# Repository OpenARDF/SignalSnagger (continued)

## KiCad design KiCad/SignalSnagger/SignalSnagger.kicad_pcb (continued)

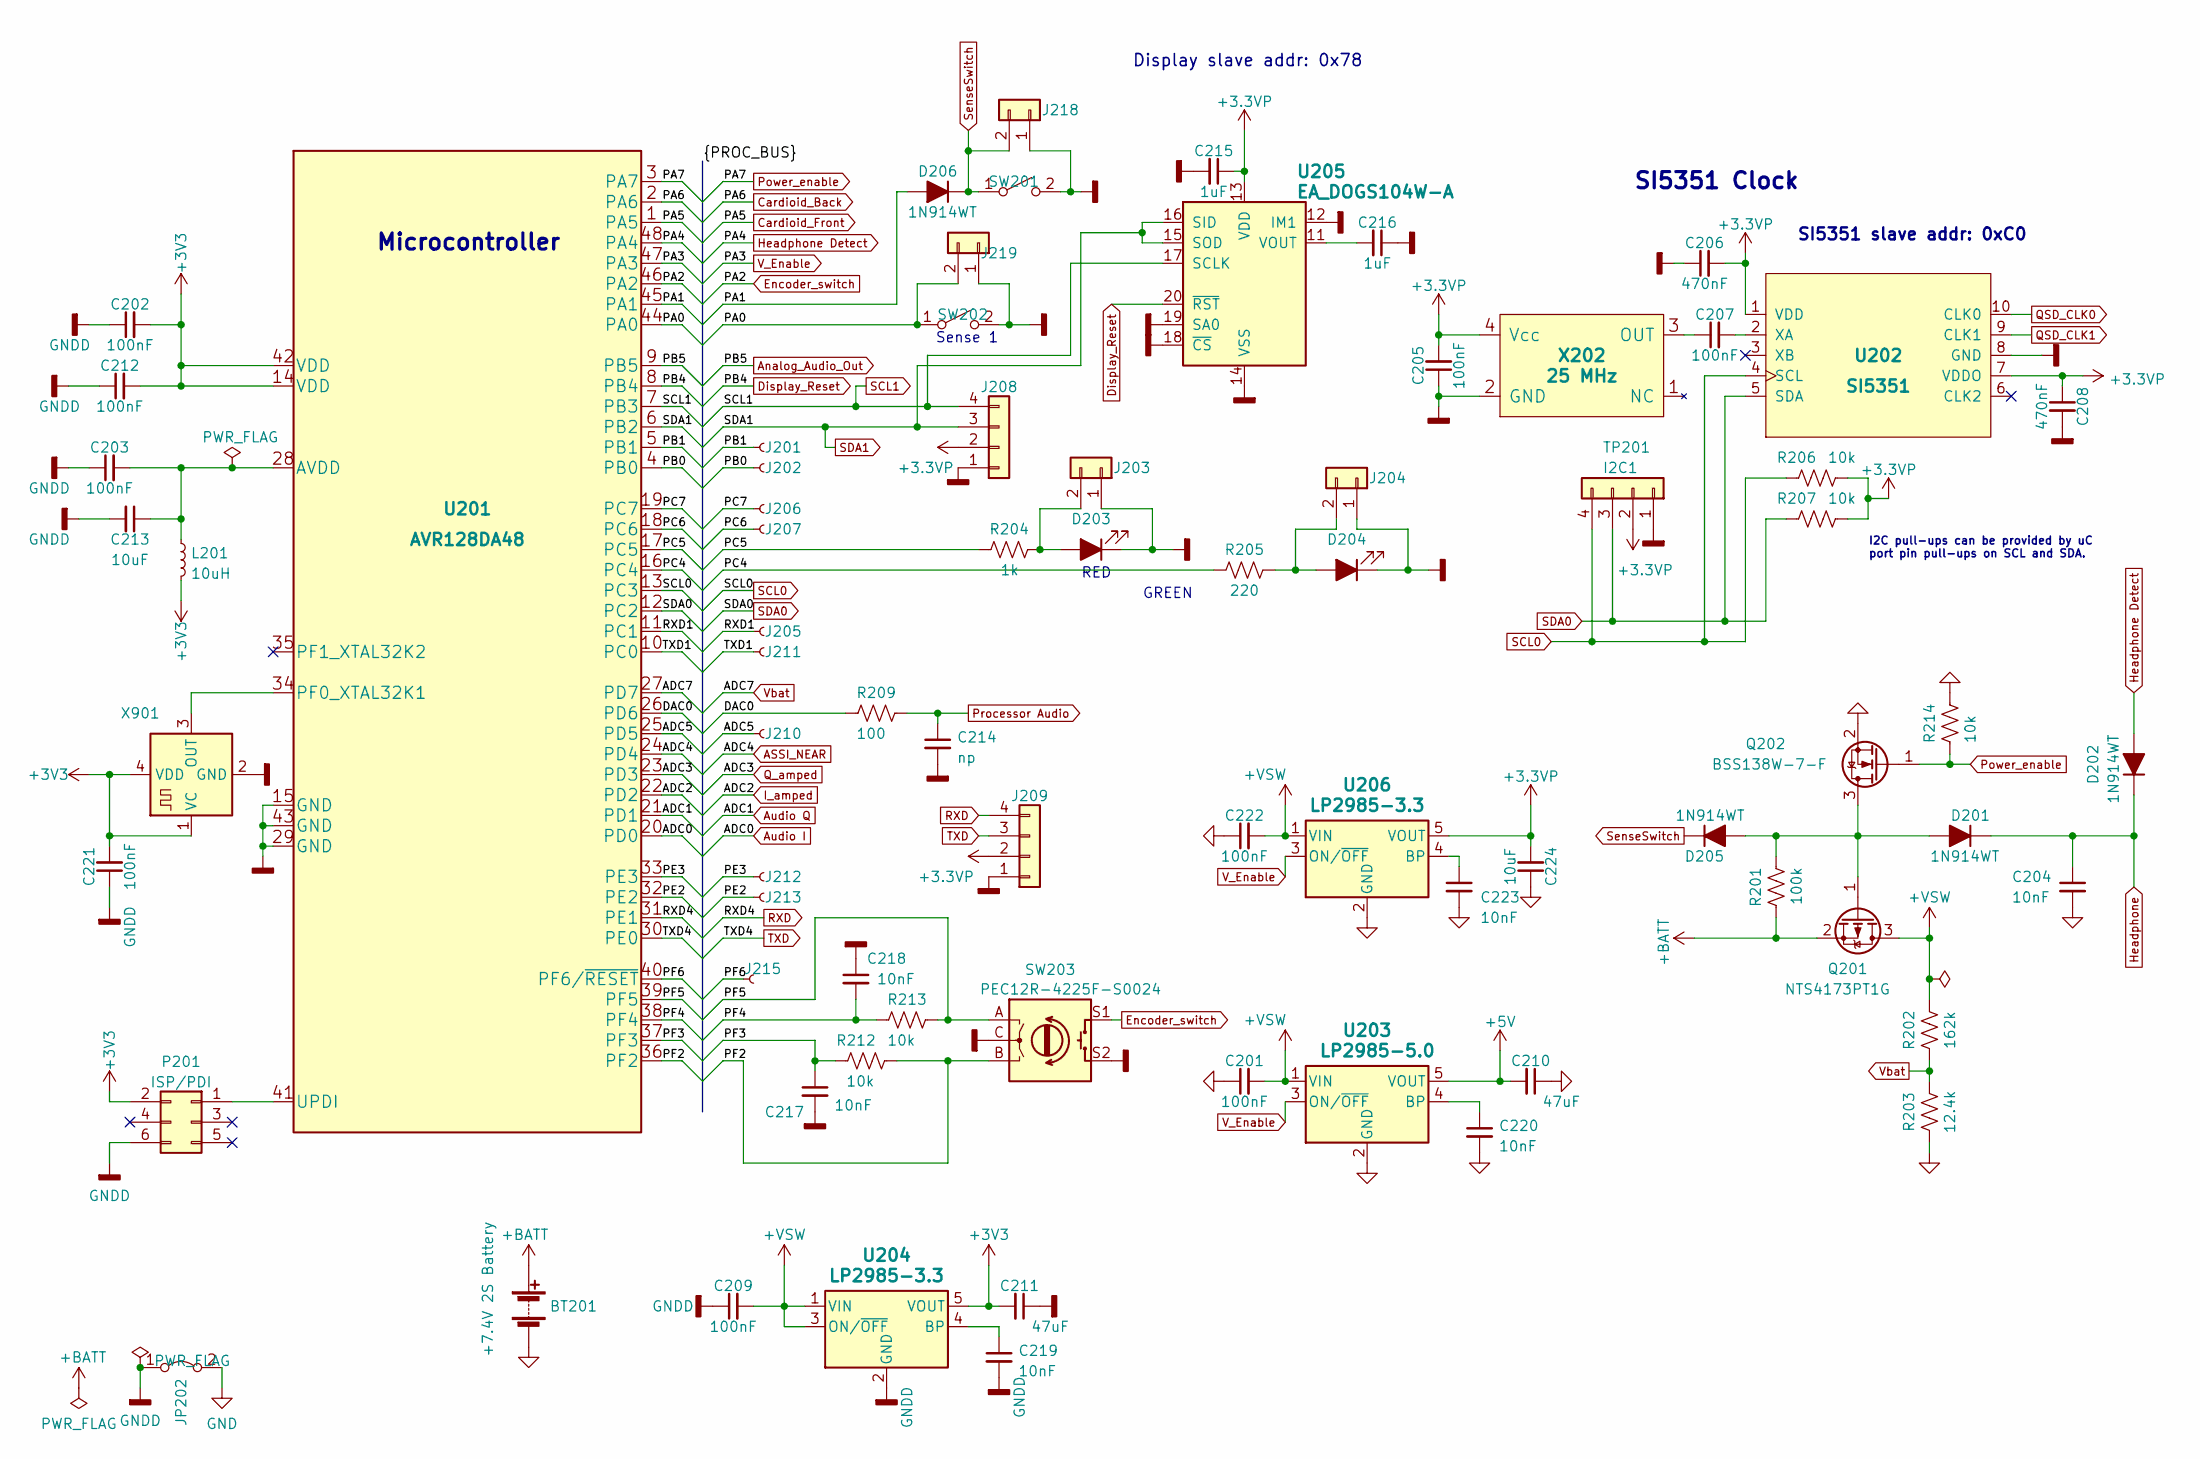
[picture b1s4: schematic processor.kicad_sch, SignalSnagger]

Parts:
BT201: +7.4V 2S Battery; SolderWire-1sqmm_1x02_P7.8mm_D1.4mm_OD3.9mm_Relief; Digi-Key Part No. NP
C201, C202, C203, C205, C207, C209, C212, C221, C222: 100nF; C_0603_1608Metric; Manufacturer PN CL10B104KA8NNNC; Digi-Key Part No. 1276-1006-1-ND
C204, C217, C218, C219, C220, C223: 10nF; C_0603_1608Metric; Manufacturer PN GRM1885C1H103JA01D; Digi-Key Part No. 490-9666-1-ND
C206, C208: 470nF; C_0603_1608Metric; Manufacturer PN CL10B474KA8VPJC; Digi-Key Part No. 1276-CL10B474KA8VPJCCT-ND
C210, C211: 47uF; C_1210_3225Metric; Manufacturer PN CL32A476KOJNNNE; Digi-Key Part No. 1276-3376-1-ND
C213, C224: 10uF; C_0603_1608Metric; Manufacturer PN GRM188C81C106MA73D; Digi-Key Part No. 490-7198-1-ND
C214: np; C_0603_1608Metric; Manufacturer PN C0603X103J4HACAUTO; Digi-Key Part No. 399-C0603X103J4HACAUTOCT-ND
C215, C216: 1uF; C_0603_1608Metric; Manufacturer PN CC0603KRX5R8BB105; Digi-Key Part No. 311-1445-1-ND
D201, D202, D205, D206: 1N914WT; D_SOD-523; Manufacturer PN 1N4148WT-7; Digi-Key Part No. 1N4148WTDICT-ND
D203: Red LED; LED_0805_2012Metric; Manufacturer PN LTST-C170KRKT; Digi-Key Part No. 160-1415-1-ND
D204: Green LED; LED_0805_2012Metric; Manufacturer PN LTST-C170KGKT; Digi-Key Part No. 160-1414-1-ND
J201, J202, J205, J206, J207, J210, J211, J212, J213, J215: Conn_01x01_Female; Dummy_Empty
J203, J204, J218, J219: Conn_01x02; PinSocket_1x02_P1.27mm_Vertical; Digi-Key Part No. N/P
J208, J209: Conn_01x04; PinHeader_1x04_P1.27mm_Vertical
JP202: Jumper_2_Bridged; Jumper_THT-1x02_Bridged_Circular; Digi-Key Part No. N/P
L201: 10uH; L_0603_1608Metric; Manufacturer PN LBMF1608T100K; Digi-Key Part No. 587-1714-1-ND
P201: ISP/PDI; PinHeader_2x03_P2.54mm_Vertical_SMD; Manufacturer PN M20-8760442; Digi-Key Part No. M20-8760442-ND
Q201: NTS4173PT1G; SOT-323_SC-70; Manufacturer PN NTS4173PT1G; Digi-Key Part No. NTS4173PT1GOSCT-ND
Q202: BSS138W-7-F; SOT-323_SC-70; Manufacturer PN BSS138W-7-F; Digi-Key Part No. BSS138W-FDICT-ND
R201: 100k; R_0603_1608Metric; Manufacturer PN RC0603FR-07100KL; Digi-Key Part No. 311-100KHRCT-ND
R202: 162k; R_0603_1608Metric; Manufacturer PN RC0603FR-07162KL; Digi-Key Part No. 311-162KHRCT-ND
R203: 12.4k; R_0603_1608Metric; Manufacturer PN RC0603FR-0712K4L; Digi-Key Part No. 311-12.4KHRCT-ND
R204: 1k; R_0603_1608Metric; Manufacturer PN RC0603FR-071KL; Digi-Key Part No. 311-1.00KHRCT-ND
R205: 220; R_0603_1608Metric; Manufacturer PN RC0603FR-07220RL; Digi-Key Part No. 311-220HRCT-ND
R206, R207, R212, R213, R214: 10k; R_0603_1608Metric; Manufacturer PN RC0603FR-0710KL; Digi-Key Part No. 311-10.0KHRCT-ND
R209: 100; R_0603_1608Metric; Manufacturer PN RC0603FR-07100RL; Digi-Key Part No. 311-100HRCT-ND
SW201, SW202: SW_SPST; SW_SPST_TL1014BF160QG; Manufacturer PN TL1014BF160QG; Digi-Key Part No. EG5042CT-ND
SW203: PEC12R-4225F-S0024; RotaryEncoder_Bourns_PEC12R-Switch_Vertical_CircularMountin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; Manufacturer PN PEC12R-4225F-S0024; Digi-Key Part No. PEC12R-4225F-S0024-ND
TP201: I2C1; PinSocket_1x04_P1.27mm_Vertical; Digi-Key Part No. N/P
U201: AVR128DA48; TQFP-48_7x7mm_P0.5mm; Manufacturer PN AVR128DA48T-E/PT; Digi-Key Part No. 150-AVR128DA48T-E/PTCT-ND
U202: SI5351; MSOP-10_3x3mm_P0.5mm; Manufacturer PN SI5351A-B-GT; Digi-Key Part No. 336-2399-5-ND
U203: LP2985-5.0; SOT-23-5; Manufacturer PN LP2985-50DBVR; Digi-Key Part No. 296-20717-1-ND
U204, U206: LP2985-3.3; SOT-23-5; Manufacturer PN LP2985-33DBVR; Digi-Key Part No. 296-18476-1-ND
U205: EA_DOGS104W-A; EA_DOGS104X-A; Manufacturer PN EA DOGS104W-A; Digi-Key Part No. 1481-1233-ND
X202: 25 MHz; Crystal_SMD_TXETCLSANF-4Pin; Manufacturer PN TXETCLSANF-25.000000; Digi-Key Part No. 1664-1273-1-ND
X901: ECS-327TXO-30-TR; Oscillator_SMD_ECS_327TXO; Manufacturer PN ECS-327TXO-30-TR; Digi-Key Part No. 50-ECS-327TXO-30-CT-ND

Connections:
+3.3VP: C205.2, C206.2, C208.1, C215.1, C224.2, J208.2, J209.2, R206.1, R207.1, TP201.2, U202.1 (VDD), U202.7 (VDDO), U205.13 (VDD), U206.5 (VOUT), X202.4 (Vcc)
+3V3: C202.2, C211.2, C212.2, C221.2, L201.2, P201.2, U201.14 (VDD), U201.42 (VDD), U204.5 (VOUT), X901.1 (VC), X901.4 (VDD)
+5V: C210.2, U203.5 (VOUT); also elsewhere on the board
+BATT: BT201.2 (+), Q201.2 (S), R201.1
+VSW: C201.2, C209.2, C222.2, Q201.3 (D), R202.2, U203.1 (VIN), U204.1 (VIN), U204.3 (ON/~OFF), U206.1 (VIN); also elsewhere on the board
/Processor/ADC5: J210.1, U201.25 (PD5)
/Processor/DAC0: R209.1, U201.26 (PD6)
/Processor/PA0: J219.2, SW202.1 (A), U201.44 (PA0)
/Processor/PA1: D206.2 (A), U201.45 (PA1)
/Processor/PB0: J202.1, U201.4 (PB0)
/Processor/PB1: J201.1, U201.5 (PB1)
/Processor/PC4: R205.1, U201.16 (PC4)
/Processor/PC5: R204.1, U201.17 (PC5)
/Processor/PC6: J207.1, U201.18 (PC6)
/Processor/PC7: J206.1, U201.19 (PC7)
/Processor/PE2: J213.1, U201.32 (PE2)
/Processor/PE3: J212.1, U201.33 (PE3)
/Processor/PF2: R212.1, SW203.B, U201.36 (PF2)
/Processor/PF3: C217.1, R212.2, U201.37 (PF3)
/Processor/PF4: C218.2, R213.2, U201.38 (PF4)
/Processor/PF5: R213.1, SW203.A, U201.39 (PF5)
/Processor/PF6: J215.1, U201.40 (PF6/~RESET)
/Processor/RXD1: J205.1, U201.11 (PC1)
/Processor/TXD1: J211.1, U201.10 (PC0)
ASSI_NEAR: U201.24 (PD4); also elsewhere on the board
Analog_Audio_Out: U201.9 (PB5); also elsewhere on the board
Audio I: U201.20 (PD0); also elsewhere on the board
Audio Q: U201.21 (PD1); also elsewhere on the board
Cardioid_Back: U201.2 (PA6); also elsewhere on the board
Cardioid_Front: U201.1 (PA5); also elsewhere on the board
Display_Reset: U201.8 (PB4), U205.20 (~RST)
Encoder_switch: SW203.S1, U201.46 (PA2)
GND: BT201.1 (-), C201.1, C204.2, C210.1, C220.2, C222.1, C223.2, C224.1, JP202.2 (B), Q202.2 (S), R203.1, R214.1, U203.2 (GND), U206.2 (GND); also elsewhere on the board
GNDD: C202.1, C203.1, C205.1, C206.1, C208.2, C209.1, C211.1, C212.1, C213.2, C214.2, C215.2, C216.1, C217.2, C218.1, C219.2, C221.1, D203.1 (K), D204.1 (K), J203.1, J204.1, J208.1, J209.1, J218.1, J219.1, JP202.1 (A), P201.6, SW201.2 (B), SW202.2 (B), SW203.C, SW203.S2, TP201.1, U201.15 (GND), U201.29 (GND), U201.43 (GND), U202.8 (GND), U204.2 (GND), U205.12 (IM1), U205.14 (VSS), U205.18 (~CS), U205.19 (SA0), X202.2 (GND), X901.2 (GND)
Headphone: C204.1, D201.1 (K), D202.1 (K); also elsewhere on the board
Headphone Detect: D202.2 (A), U201.48 (PA4)
I_amped: U201.22 (PD2); also elsewhere on the board
unnamed: D201.2 (A), D205.2 (A), Q201.1 (G), Q202.3 (D), R201.2
unnamed: D203.2 (A), J203.2, R204.2
unnamed: D204.2 (A), J204.2, R205.2
unnamed: P201.1, U201.41 (UPDI)
unnamed: C203.2, C213.1, L201.1, U201.28 (AVDD)
unnamed: U201.34 (PF0_XTAL32K1), X901.3 (OUT)
unnamed: C207.2, U202.2 (XA)
unnamed: C220.1, U203.4 (BP)
unnamed: C219.1, U204.4 (BP)
unnamed: C216.2, U205.11 (VOUT)
unnamed: C223.1, U206.4 (BP)
unnamed: C207.1, X202.3 (OUT)
Power_enable: Q202.1 (G), R214.2, U201.3 (PA7)
Processor Audio: C214.1, R209.2; also elsewhere on the board
QSD_CLK0: U202.10 (CLK0); also elsewhere on the board
QSD_CLK1: U202.9 (CLK1); also elsewhere on the board
Q_amped: U201.23 (PD3); also elsewhere on the board
RXD: J209.4, U201.31 (PE1)
SCL0: R206.2, TP201.4, U201.13 (PC3), U202.4 (SCL); also elsewhere on the board
SCL1: J208.4, U201.7 (PB3), U205.17 (SCLK); also elsewhere on the board
SDA0: R207.2, TP201.3, U201.12 (PC2), U202.5 (SDA); also elsewhere on the board
SDA1: J208.3, U201.6 (PB2), U205.15 (SOD), U205.16 (SID); also elsewhere on the board
SenseSwitch: D205.1 (K), D206.1 (K), J218.2, SW201.1 (A)
TXD: J209.3, U201.30 (PE0)
V_Enable: U201.47 (PA3), U203.3 (ON/~OFF), U206.3 (ON/~OFF)
Vbat: R202.1, R203.2, U201.27 (PD7)

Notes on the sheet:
I2C pull-ups can be provided by uC port pin pull-ups on SCL and SDA.
GREEN
Display slave addr: 0x78
Sense 1
RED
SI5351 slave addr: 0xC0
Microcontroller
SI5351 Clock

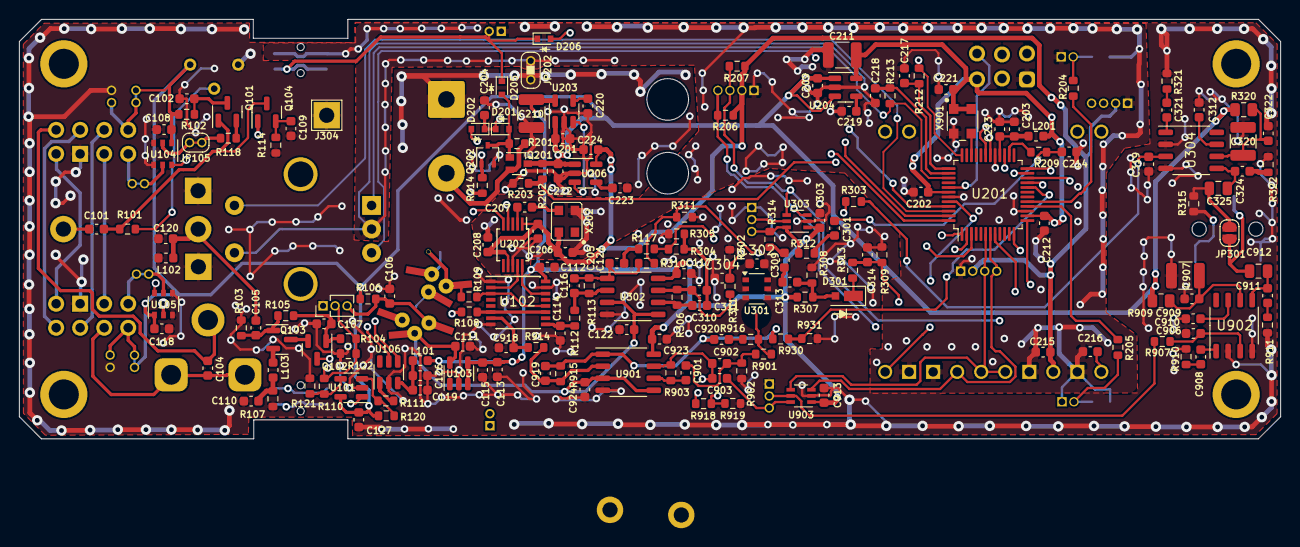
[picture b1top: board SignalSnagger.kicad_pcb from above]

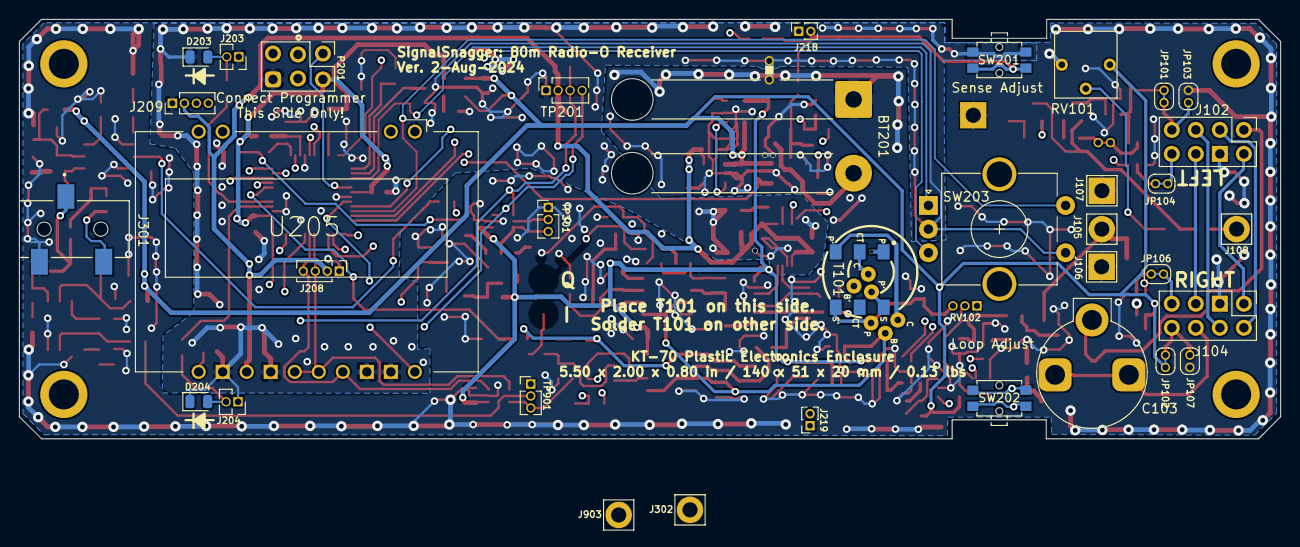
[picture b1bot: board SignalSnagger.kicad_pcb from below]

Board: 4 copper layers, 133.4 x 44.3 mm, 217 parts (36 on the bottom side), 132 nets.

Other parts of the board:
T901: Coilcraft_PWB-4-CLC; Coilcraft-PWB-4-CLC

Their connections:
unnamed 89: T901.4 (SB); also elsewhere on the board
Vref: T901.2 (P_CT); also elsewhere on the board

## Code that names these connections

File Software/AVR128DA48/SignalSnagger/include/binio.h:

/*
 *  MIT License
 *
 *  Copyright (c) 2022 DigitalConfections
 *
 *  Permission is hereby granted, free of charge, to any person obtaining a copy
 *  of this software and associated documentation files (the "Software"), to deal
 *  in the Software without restriction, including without limitation the rights
 *  to use, copy, modify, merge, publish, distribute, sublicense, and/or sell
 *  copies of the Software, and to permit persons to whom the Software is
 *  furnished to do so, subject to the following conditions:
 *
 *  The above copyright notice and this permission notice shall be included in all
 *  copies or substantial portions of the Software.
 *
 *  THE SOFTWARE IS PROVIDED "AS IS", WITHOUT WARRANTY OF ANY KIND, EXPRESS OR
 *  IMPLIED, INCLUDING BUT NOT LIMITED TO THE WARRANTIES OF MERCHANTABILITY,
 *  FITNESS FOR A PARTICULAR PURPOSE AND NONINFRINGEMENT. IN NO EVENT SHALL THE
 *  AUTHORS OR COPYRIGHT HOLDERS BE LIABLE FOR ANY CLAIM, DAMAGES OR OTHER
 *  LIABILITY, WHETHER IN AN ACTION OF CONTRACT, TORT OR OTHERWISE, ARISING FROM,
 *  OUT OF OR IN CONNECTION WITH THE SOFTWARE OR THE USE OR OTHER DEALINGS IN THE
 *  SOFTWARE.
 */


#ifndef __BINIO_H__
#define __BINIO_H__

#include "defs.h"

/* PORTA *************************************************************************************/
#define POWER_ENABLE 7
#define CARDIOID_BACK 6
#define CARDIOID_FRONT 5
#define HEADPHONE_DETECT 4
#define PWR_5V_ENABLE 3
#define ENCODER_SWITCH 2
#define SENSE_SWITCH_LEFT 1
#define SENSE_SWITCH_RIGHT 0

/* PORTB *************************************************************************************/
#define J210 5
#define LCD_RESET 4
#define J216 3
#define J217 2
#define J201 1
#define J202 0

/* PORTC *************************************************************************************/
#define J206 7
#define J207 6
#define LED_RED_1 5
#define LED_GREEN_1 4
#define SI5351_SCL0 3
#define SI5351_SDA0 2
#define J205 1
#define J211 0

/* PORTD *************************************************************************************/
#define BATT_VOLTAGE_PIN 7
#define DAC_OUTPUT_PIN 6
#define ASSI_FAR_PIN 5
#define ASSI_NEAR_PIN 4
#define Q_AMPED_PIN 3
#define I_AMPED_PIN 2
#define Q_AUDIO_PIN 1
#define I_AUDIO_PIN 0

/* PORTE *************************************************************************************/
#define PWM 2

/* PORTF *************************************************************************************/
#define J215 6
#define ROTARY_A 5
#define ROTARY_A_IN 4
#define ROTARY_B_IN 3
#define ROTARY_B 2
#define X32KHZ_SQUAREWAVE 0


void BINIO_init(void);
void BINIO_sleep(void);
void debounce(void);
uint8_t portAdebouncedVals(void);
uint8_t portFdebouncedVals(void);

class binio
{
//variables
public:
protected:
private:

//functions
public:
	binio();
	~binio();
protected:
private:
	binio( const binio &c );
	binio& operator=( const binio &c );

}; //binio

#endif //__BINIO_H__

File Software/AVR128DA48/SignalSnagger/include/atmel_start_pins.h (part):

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*************************************************************************************/

/**
 * \brief Set PA0 pull mode
 *
 * Configure pin to pull up, down or disable pull mode, supported pull
 * modes are defined by device used
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}

/**
 * \brief Set PA0 data direction
 *
 * Select if the pin data direction is input, output or disabled.
 * If disabled state is not possible, this function throws an assert.
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}

/**
 * \brief Set PA0 input/sense configuration
 *
 * Enable/disable PA0 digital input buffer and pin change interrupt,
 * select pin interrupt edge/level sensing mode
 *
 * \param[in] isc PORT_ISC_INTDISABLE_gc    = Iterrupt disabled but input buffer enabled
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}

/**
 * \brief Set PA0 inverted mode
 *
 * Enable or disable inverted I/O on a pin
 *
 * \param[in] inverted true  = I/O on PA0 is inverted
 *                     false = I/O on PA0 is not inverted
 */
static inline void PA0_set_inverted(const bool inverted)
{
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}

/**
 * \brief Set PA0 level
 *
 * Sets output level on a pin
 *
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}

/**
 * \brief Toggle output level on PA0
 *
 * Toggle the pin level
 */
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}

/**
 * \brief Get level on PA0
 *
 * Reads the level on a pin
 */
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}

/**
 * \brief Set PA1 pull mode
 *
 * Configure pin to pull up, down or disable pull mode, supported pull
 * modes are defined by device used
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}

/**
 * \brief Set PA1 data direction
 *
 * Select if the pin data direction is input, output or disabled.
 * If disabled state is not possible, this function throws an assert.
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}

/**
 * \brief Set PA1 input/sense configuration
 *
 * Enable/disable PA1 digital input buffer and pin change interrupt,
 * select pin interrupt edge/level sensing mode
 *
 * \param[in] isc PORT_ISC_INTDISABLE_gc    = Iterrupt disabled but input buffer enabled
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}

/**
 * \brief Set PA1 inverted mode
 *
 * Enable or disable inverted I/O on a pin
 *
 * \param[in] inverted true  = I/O on PA1 is inverted
 *                     false = I/O on PA1 is not inverted
 */
static inline void PA1_set_inverted(const bool inverted)
{
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}

/**
 * \brief Set PA1 level
 *
 * Sets output level on a pin
 *
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}

/**
 * \brief Toggle output level on PA1
 *
 * Toggle the pin level
 */
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}

/**
 * \brief Get level on PA1
 *
 * Reads the level on a pin
 */
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}

/**
 * \brief Set PC0 pull mode
 *
 * Configure pin to pull up, down or disable pull mode, supported pull
 * modes are defined by device used
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}

/**
 * \brief Set PC0 data direction
 *
 * Select if the pin data direction is input, output or disabled.
 * If disabled state is not possible, this function throws an assert.
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}

/**
 * \brief Set PC0 input/sense configuration
 *
 * Enable/disable PC0 digital input buffer and pin change interrupt,
 * select pin interrupt edge/level sensing mode
 *
 * \param[in] isc PORT_ISC_INTDISABLE_gc    = Iterrupt disabled but input buffer enabled
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}

/**
 * \brief Set PC0 inverted mode
 *
 * Enable or disable inverted I/O on a pin
 *
 * \param[in] inverted true  = I/O on PC0 is inverted
 *                     false = I/O on PC0 is not inverted
 */
static inline void PC0_set_inverted(const bool inverted)
{
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}

/**
 * \brief Set PC0 level
 *
 * Sets output level on a pin
 *
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}

/**
 * \brief Toggle output level on PC0
 *
 * Toggle the pin level
 */
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}

/**
 * \brief Get level on PC0
 *
 * Reads the level on a pin
 */
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}

/**
 * \brief Set PC1 pull mode
 *
 * Configure pin to pull up, down or disable pull mode, supported pull
 * modes are defined by device used
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}

/**
 * \brief Set PC1 data direction
 *
 * Select if the pin data direction is input, output or disabled.
 * If disabled state is not possible, this function throws an assert.
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}

/**
 * \brief Set PC1 input/sense configuration
 *
 * Enable/disable PC1 digital input buffer and pin change interrupt,
 * select pin interrupt edge/level sensing mode
 *
 * \param[in] isc PORT_ISC_INTDISABLE_gc    = Iterrupt disabled but input buffer enabled
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}

/**
 * \brief Set PC1 inverted mode
 *
 * Enable or disable inverted I/O on a pin
 *
 * \param[in] inverted true  = I/O on PC1 is inverted
 *                     false = I/O on PC1 is not inverted
 */
static inline void PC1_set_inverted(const bool inverted)
{
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}

/**
 * \brief Set PC1 level
 *
 * Sets output level on a pin
 *
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}

/**
 * \brief Toggle output level on PC1
 *
 * Toggle the pin level
 */
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}

/**
 * \brief Get level on PC1
 *
 * Reads the level on a pin
 */
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*************************************************************************************/

/**
 * \brief Set PE0 pull mode
 *
 * Configure pin to pull up, down or disable pull mode, supported pull
 * modes are defined by device used
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}

/**
 * \brief Set PE0 data direction
 *
 * Select if the pin data direction is input, output or disabled.
 * If disabled state is not possible, this function throws an assert.
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}

/**
 * \brief Set PE0 input/sense configuration
 *
 * Enable/disable PE0 digital input buffer and pin change interrupt,
 * select pin interrupt edge/level sensing mode
 *
 * \param[in] isc PORT_ISC_INTDISABLE_gc    = Iterrupt disabled but input buffer enabled
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}

/**
 * \brief Set PE0 inverted mode
 *
 * Enable or disable inverted I/O on a pin
 *
 * \param[in] inverted true  = I/O on PE0 is inverted
 *                     false = I/O on PE0 is not inverted
 */
static inline void PE0_set_inverted(const bool inverted)
{
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}

/**
 * \brief Set PE0 level
 *
 * Sets output level on a pin
 *
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}

/**
 * \brief Toggle output level on PE0
 *
 * Toggle the pin level
 */
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}

/**
 * \brief Get level on PE0
 *
 * Reads the level on a pin
 */
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}

/**
 * \brief Set PE1 pull mode
 *
 * Configure pin to pull up, down or disable pull mode, supported pull
 * modes are defined by device used
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}

/**
 * \brief Set PE1 data direction
 *
 * Select if the pin data direction is input, output or disabled.
 * If disabled state is not possible, this function throws an assert.
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}

/**
 * \brief Set PE1 input/sense configuration
 *
 * Enable/disable PE1 digital input buffer and pin change interrupt,
 * select pin interrupt edge/level sensing mode
 *
 * \param[in] isc PORT_ISC_INTDISABLE_gc    = Iterrupt disabled but input buffer enabled
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}

/**
 * \brief Set PE1 inverted mode
 *
 * Enable or disable inverted I/O on a pin
 *
 * \param[in] inverted true  = I/O on PE1 is inverted
 *                     false = I/O on PE1 is not inverted
 */
static inline void PE1_set_inverted(const bool inverted)
{
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}

/**
 * \brief Set PE1 level
 *
 * Sets output level on a pin
 *
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}

/**
 * \brief Toggle output level on PE1
 *
 * Toggle the pin level
 */
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}

/**
 * \brief Get level on PE1
 *
 * Reads the level on a pin
 */
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
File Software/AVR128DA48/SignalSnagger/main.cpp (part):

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				!g_frequency_updates_enabled && !g_suppress_cardioid_until_side_release);
			g_cardioid_front_enabled = senseSwitches.cardioidFrontEnabled;
			g_cardioid_back_enabled = senseSwitches.cardioidBackEnabled;
			PORTA_set_pin_level(CARDIOID_FRONT, senseSwitches.cardioidFrontEnabled ? HIGH : LOW);
			PORTA_set_pin_level(CARDIOID_BACK, senseSwitches.cardioidBackEnabled ? HIGH : LOW);
			
			g_encoderswitch_pressed = !encoderSwitch;
			g_leftsense_pressed = senseSwitches.leftPressed;
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			prev_state = curr_state;
		}
	}
    // Clear the interrupt flags for PF3 and PF4
    PORTF.INTFLAGS = PIN3_bm | PIN4_bm;
}

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	rollbackMenuEditsIfActive();
	EEPromMgr.saveAllEEPROM();
	PORTA_set_pin_level(PWR_5V_ENABLE, LOW);	
	PORTA_set_pin_level(POWER_ENABLE, LOW);
	
	int poweroff = 100;
	
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				if(g_headphones_detected)
				{
					PORTA_set_pin_level(PWR_5V_ENABLE, HIGH);  /* Enable 5V power regulator */
					PORTA_set_pin_level(POWER_ENABLE, HIGH);
				}
			}
		}
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
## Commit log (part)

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2023-11-04 First KiCad Upload
    Version 0.2
2023-11-04 Schematic Update
    Development
2023-11-04 Schematic Update
2023-11-04 Schematic Updates
    Development
2023-11-05 Schematic Update
    DF Antenna Corrections
2023-11-05 Ver 0.6
    Schematic updates
2023-11-05 Ver 0.6
    Re-annotated and ERC'd
2023-11-05 Ver 0.7
    Schematic update
2023-11-05 Ver 0.9
    Schematic corrections and cleanup
2023-11-05 Schematic Updates
    Cleanup
2023-11-05 Ver 0.10
    More schematic cleanup
2023-11-06 Rev 0.11
    o Added missing DF loop center tap ground
2023-11-06 Ver 0.12
    Added antenna diagram sheet.
2023-11-09 Ver 0.15
    Schematic changes
2023-12-11 Schematic Updates
    Added display and rotary encoder
    Added Jerry's changes based on testing
2023-12-19 Schematic Updates
    Rev 0.18
2023-12-19 Annotated Schematic
2023-12-19 Schematic Tweaks
2023-12-20 Schematic Updates
    First cut at prototype design
2023-12-20 Schematic Update
    Added +5V processor control
2023-12-30 Removed Warnings
    Trivial changes to remove DRC warnings
2024-02-02 Ver 0.22
    o Schematic updates
2024-02-03 Stereo Support
    Updates to Audio schematic to reflect discussions regarding stereo support.
2024-02-04 Ver 0.24
    Schematic updates.
2024-02-09 V0.25
    Schematic updates
2024-02-10 V0.26
    Changes to rotary encoder debounce.
2024-02-10 V 0.27
    More updates to rotary encoder interface.
2024-02-10 Update SignalSnagger.kicad_pcb
    Added KT-70 PCB outline into PCB Editor
2024-02-16 Rev 0.28
    Adding footprints to schematic: ~10% done
2024-02-17 Ver 0.29
    Schematic updates
2024-03-07 Minor Cleanup
    No functional changes, only cosmetic changes to the schematic
2024-03-11 Schematic Updates
    Adding part numbers and footprints
2024-03-11 Schematic updates
    Fixes to 10uF capacitors - now they are X6S size 0603.
2024-03-12 Schematic Updates
    Ver 0.300
    All parts have been assigned DigiKey part numbers where appropriate, and have reasonable (but perhaps not perfect) footprints assigned to them.
2024-03-12 Rev 0.301
    PCB Updates - first import from schematic
    Schematic Updates - fixes for various footprints
2024-03-15 PCB & Schematic Updates
    Removed parts not targeted for first prototype
    Made other changes discussed in Zoom call
    Updated BOM
    Updated PCB with new parts list
    Noodled with parts placement on PCB
2024-03-15 Ver 0.303
    Schematic and PCB updates.
    Added R122.
2024-03-15 Ver 0.303
2024-03-15 Ver 0.304
    Schematic fixes
    PCB updates
2024-03-15 Ver 0.305
    PCB Layout Changes
2024-03-16 PCB Updates
    Ver 0.306
    Brought in Jerry's layout of RF components.
2024-03-16 Ver 0.307
    PCB updates
    o All components are now placed onto the board with not traces drawn
    oRe-added the stereo channel. Parts are numbered starting with 901, so they can be easily identified for not populating or future removal
2024-03-17 Ver 0.308
    Schematic and PCB tweaks
    Set board thickness to 1.6mm
2024-03-18 Ver 0.309
    PCB layout updates
    Schematic updates
2024-03-19 Ver 0.310
    Schematic and PCB updates
2024-03-27 Ver 0.311
    Schematic and PCB updates
    All PCB connections have been made
    Design rule check returns no errors or warnings
    Still need to examine footprints, trace widths, pour coverage, etc.
    First Gerbers built
2024-03-29 Ver 0.312
    PCB updates
    BOM updates
    Schematic updates
2024-03-30 Rev 0.313
    Schematic, BOM, and PCB updates to add sense switch power-on feature.
2024-03-30 Gerber Updates
    Fixes to Gerber files
2024-03-31 Ver 0.314
    Corrected footprint for U102
2024-04-01 PCB Updates
    31-Mar-2024
2024-04-01 Ver 0.315
    BOM update
2024-04-06 Update SignalSnagger.kicad_pcb
    Moved headphones jack to back of PCB
2024-04-06 PCB Updates
    Moved programming header
    Added ribbon cable plugs
2024-04-12 PCB Layout
    Most 3D models have been included in the schematic
    PCB layout places all tall parts on the back of the board
    Added knob to BOM
2024-04-13 Ver 0.317
    PCB Tweaks
    FreeCAD model updates
2024-04-17 Removed spare sense switches
    Updated schematic and PCB to remove spare sense switches.
2024-04-23 Gerber Update
    Updated Gerbers to latest PCB version.
2024-04-23 Update SignalSnagger.zip
    No changes other than the new SignalSnagger.zip containing Gerbers.
2024-04-25 Gerber rebuild
    Rebuilt all Gerber files again to ensure they are all up to date, including the zip file.
2024-04-29 BOM Updates
2024-05-04 Schematic PDF File
    Updated date on schematic and printed an updated PDF schematic. No changes made to design.
2024-05-15 Added Software Folder
    Software to support board bring-up
2024-05-17 Ver 0.02
    o Si5351 clock out from both clock0 and clock1
    o Tests for 32 kHz clock operation
2024-05-17 Ver 0.03
    First attempt to set SI5351 relative phase
2024-05-17 Ver 0.04
    Offset frequency by 500 Hz
2024-05-18 Ver 0.05
    Added placeholders for Display and rotary encoder.
2024-05-21 Ver 0.06
    The following peripherals are functioning normally in this version:
    Rotary encoder
    All switches
    LEDs
2024-05-24 Snapshot
    Holding changes related to SI5351 quadrature programming
2024-05-25 Ver 0.08
    Display is now functional
2024-05-27 Ver 0.09
    o Quadrature for QSD is now working
    o Frequency is now set using the rotary encoder
    o PWM is now set using the rotary encoder
    o Frequency, PWM, and ASSI are all display on the LCD
    o Certain hardware failures are detected and indicated on the LCD
2024-06-01 Updated Schematic
    o Updated T101 to accept Coilcraft part
    o Added J208 to support an external I2C module
    o Added D206 to block battery voltage
    o Updated PCB with changes above
    o Corrected silkscreen
2024-06-01 Si5351
    Re-added use of union for generating register values from calculated 32-bit parameters.
2024-06-03 Schematic and PCB Updates
    o Changed power rating of R320 and R909
    o Changed Q201 to a 1-Amp part
    o Updated Gerbers
2024-06-03 BOM Update
    Updated BOM
2024-06-03 BOM Correction
    o Corrected the part associated with U103 (should be a 2.5V reference)
2024-06-04 PWM Changes
    o Changes to output the PWM on PE2
    o Disables PE3 and sets it as an input
    o Uses 16-bit TCA timer
    o Ver 0.10
2024-06-04 Ver 0.319
    o Shorted PE2 and PE3 together to support both 8-bit and 16-bit TCA-generated PWM
    o Added J209 to support an external module requiring RS232 comms
2024-06-06 Ver 0.11
    PWM frequency set to 24 kHz
2024-06-06 Ver 0.12
    o Sets PWM frequency to ~5 kHz
2024-06-07 PWM EMI
    Added changes to schematic and PCB layout to address EMI issues
2024-06-07 Ver 0.13
    Sets PWM frequency to 2.5 kHz
2024-06-08 June 8 Revision
    o Cleaned up PCB
    o Added stitching vias
    o Foxed T101 footprint to work with automated assembly
2024-06-09 Error fix for U101
    o Corrected pinout of U101
    o Updated schematic version to 0.320
2024-06-09 Rev 0.321
    o Added voltage divider for the I_AMPED and Q_AMPED ADC inputs to the processor.
    o Generated new Gerbers
    o Generated new BOM files
2024-06-09 Added voltage divider
    o Added voltage dividers for I_AMPED and Q_AMPED
    o Regenerated Gerbers
    o Updated schematic
    o Updated BOM files
2024-06-14 Moved TP301
    o Moved test point farther from LCD
    o Updated Gerbers
2024-06-15 PCB Updates
    o Moved sense buttons to bottom of board
    o Moved sense buttons level with rotary encoder
    o Improved component clearances and centering
2024-06-15 PCB Cleanup
    o New Gerbers
    o Silkscreen changes
    o Parts placement tweaks
2024-06-15 FreeCAD Updates
    Updated FreeCAD model with latest PCB
2024-06-15 PCB Cleanup
    More PCB tweaks
2024-06-16 Sense Switch Tweak
    o Tweaked the position of the sense switches to make them extend only the travel distance beyond the edge of the board.
    o Updated Gerbers
2024-06-19 Design Tweaks Ver 0.322
    o Added L202 to help filter noise from 10V rail
    o Moved RV302 and RV901 to the back of PCB
    o Updated Gerbers
    o Updated BOM
    o Updated schematic
2024-06-29 Ver 0.20
    o First attempt to route audio through the processor
    o All audio is sampled and passed to DAC
    o Rudimentary beeps on key release
    o Audio gain applied by processor
2024-06-30 Schematic Ver 0.323
    o Updated schematic with changes to audio sampling interface locations
    o PCB and Gerbers still need to be updated to be in sync with this schematic
2024-06-30 Ver 0.21
    Processor passes all audio to the headphones
    Some Goertzel tuning applied (more needed)
2024-07-01 Ver 0.22
    o Powers off after 60 seconds of no headphone detected
2024-07-07 Ver 0.23
    o Added 20 memory channels of frequency storage. Access with long rotary shaft press
    o Implemented a memory mode. Access with three presses on the rotary shaft
    o Changed frequency display to kHz
    o Fixes PWM frequency
    o Added an audio "tick" when rotary knob is turned
2024-07-09 Ver 0.24
    o Disable/enable audio feedthrough with double-press of right sense button
2024-07-10 Ver 0.25
    o Rotary bug fixes
    o Beginnings of menu system
2024-07-11 Ver 0.26
    o Menu improvements
2024-07-11 Ver 0.26
2024-07-11 Ver 0.27
    o Menu bug fixes
    o Supports erasing a memory channel
2024-07-11 Ver 0.28
    Fixes memory bug when no memories are programmed
    Fixes memory bug when only one memory is programmed
2024-07-12 Ver 0.30
    Added support for 1 kHz frequency steps without activating a encoder switch closure detection.
2024-07-12 Ver 0.30
    Splash screen shows battery voltage
2024-07-12 Schematic Updates
    Schematic version 0.323.
    Schematic and BOM updates only.
    For next rev PCB.
2024-07-12 Rev 0.325
    Removed +10V rail and replaced it by +VSW
2024-07-13 BOM Update
    Brought in schematic changes
    Generated new Gerbers
2024-07-13 Ver 0.31
    o Fixes ADC battery voltage sampling anomaly
    o RF gain now has 10 settings that can be individually adjusted for gain
2024-07-14 Ver 0.32
    Adds the ability to apply a name to memory channels.
2024-07-16 Ver 0.33
    o Added BATTERY menu
2024-07-17 Ver 0.34
    o Bug fixes
    o Adds the ability to set a battery warning threshold % value
    o Displays a battery warning on start-up if the battery is below the set threshold
2024-07-20 Ver 0.35
    First version with partial DSP functionality. LEDs illuminate to indicate signal detection: green = signal; red = noise
2024-08-22 Ver 0.36
    o EEPROM update - it now stores the last memory used
    o RSSI - Improvements to signal detection
    o Bug fixes
2024-08-22 Ver 0.326
    Added footprints for noise reduction changes to RF amplifier
    Removed C109
    Updated schematic, BOM, PCB and Gerbers
2024-09-11 Ver 0.37
    o Fixes some power-off bugs
    o Improves headphones removal message
    o Increases audio sample rate to 48 ksps
2024-09-13 Ver 0.38
    Increased ADC sample rate to 96154
2024-10-20 Schematic and BOM Updates
    Still need to bring these changes into the PCB.
2026-01-09 Ver 1.0
    Redesign of LED tuning indicator.
2026-02-25 Schematic & PCB Updates
    o JFET sense amp option
    o U301
    Note: PCB changes are incomplete
